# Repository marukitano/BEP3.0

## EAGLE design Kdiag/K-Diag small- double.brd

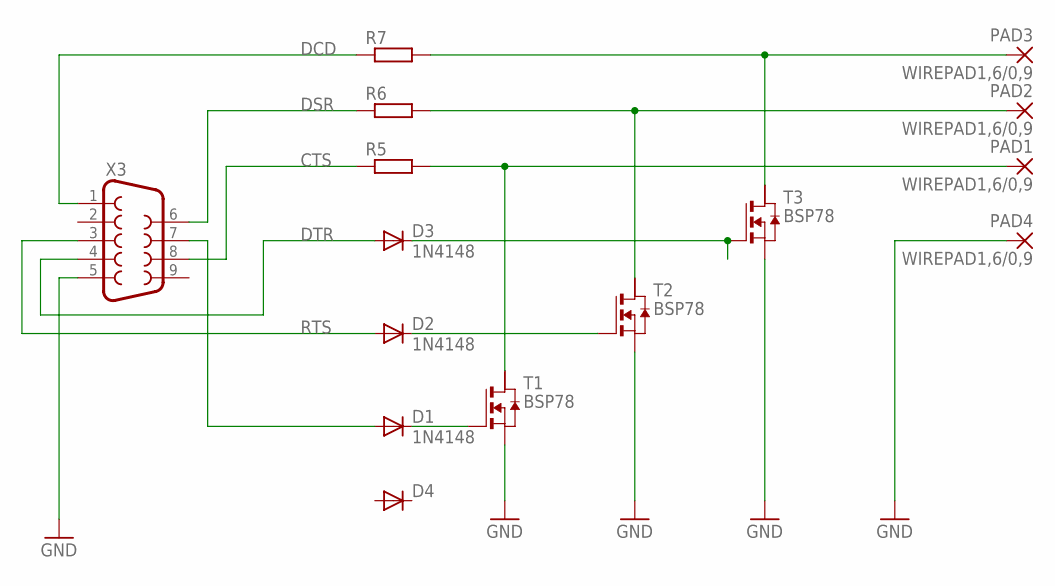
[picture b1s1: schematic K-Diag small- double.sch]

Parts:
D1, D2, D3: 1N4148; SOD323-W
D4: DIODE-SOD323-W; SOD323-W
PAD1, PAD2, PAD3, PAD4: WIREPAD1,6/0,9; 1,6/0,9
R5, R6, R7: R-EU_R0805; R0805
T1, T2, T3: BSP78; SOT223
X3: F09D

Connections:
CTS: R5.1, X3.8
DCD: R7.1, X3.1
DSR: R6.1, X3.6
DTR: D3.A, X3.4
GND: PAD4.1, T1.3 (S), T2.3 (S), T3.3 (S), X3.5
unnamed: D3.C, T3.1 (G)
unnamed: D2.C, T2.1 (G)
unnamed: D1.C, T1.1 (G)
unnamed: PAD1.1, R5.2, T1.2 (D)
unnamed: PAD2.1, R6.2, T2.2 (D)
unnamed: PAD3.1, R7.2, T3.2 (D)
unnamed: D1.A, X3.7
RTS: D2.A, X3.3

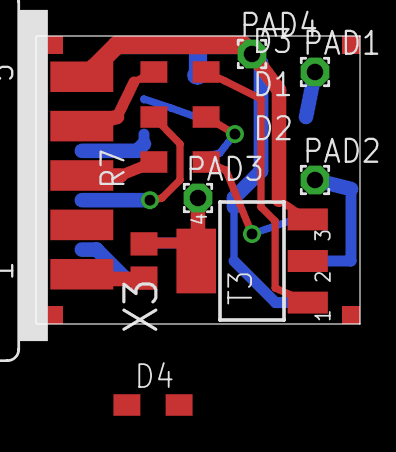
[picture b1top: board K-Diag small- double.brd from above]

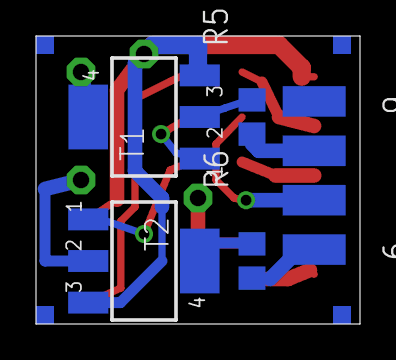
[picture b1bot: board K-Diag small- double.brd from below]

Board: 2 copper layers, 18.0 x 16.0 mm, 15 parts (4 on the bottom side), 13 nets.

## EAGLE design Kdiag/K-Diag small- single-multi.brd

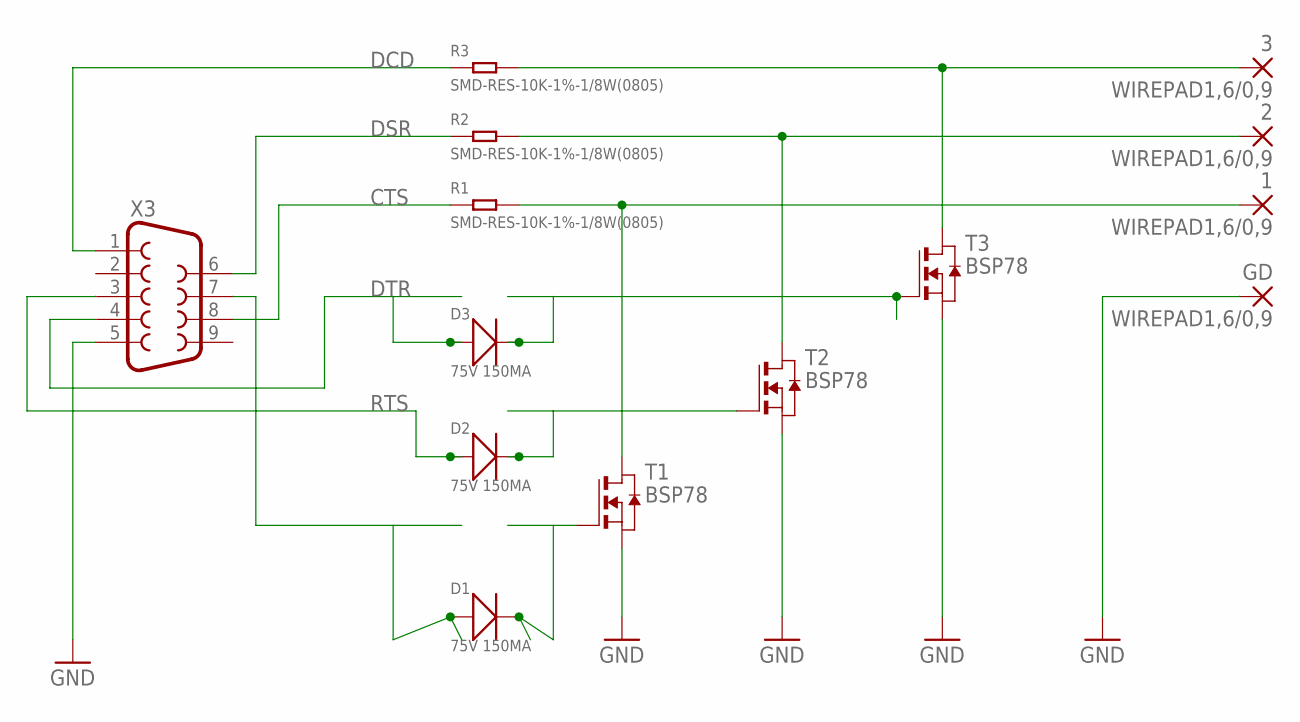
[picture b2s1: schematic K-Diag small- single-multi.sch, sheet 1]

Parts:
1, 2, 3: WIREPAD1,6/0,9; 1,6/0,9
D1, D2, D3: 75V 150MA; LED-1206
GD: WIREPAD1,6/0,9; 1,6/0,9
R1, R2, R3: SMD-RES-10K-1%-1/8W(0805); R0805
T1, T2, T3: BSP78; SOT223
X3: F09D

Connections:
CTS: R1.1, X3.8; also elsewhere on the board
DCD: R3.1, X3.1; also elsewhere on the board
DSR: R2.1, X3.6; also elsewhere on the board
DTR: D3.+, X3.4; also elsewhere on the board
GND: GD.1, T1.3 (S), T2.3 (S), T3.3 (S), X3.5; also elsewhere on the board
unnamed: D3.-, T3.1 (G)
unnamed: D2.-, T2.1 (G)
unnamed: D1.-, T1.1 (G)
unnamed: 1.1, R1.2, T1.2 (D), T1.4 (D)
unnamed: 2.1, R2.2, T2.2 (D), T2.4 (D)
unnamed: 3.1, R3.2, T3.2 (D), T3.4 (D)
unnamed: D1.+, X3.7
RTS: D2.+, X3.3; also elsewhere on the board

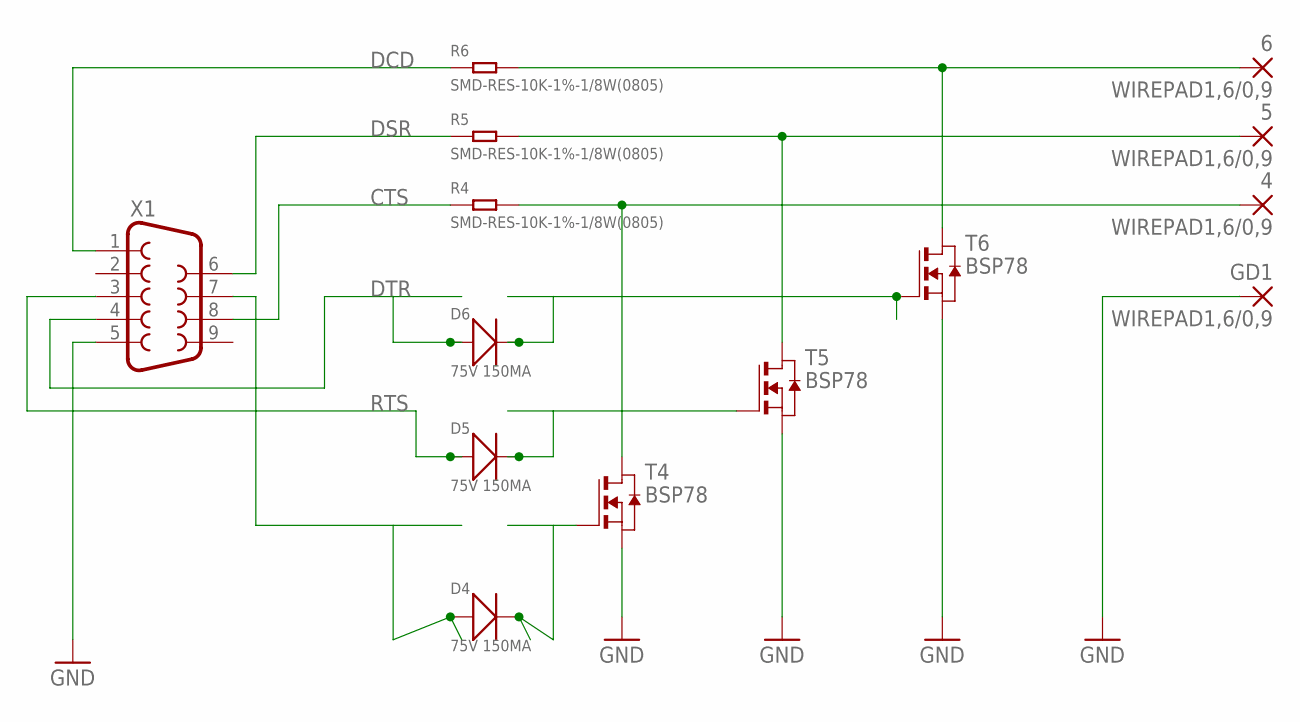
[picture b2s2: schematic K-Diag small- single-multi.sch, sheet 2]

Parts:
4, 5, 6: WIREPAD1,6/0,9; 1,6/0,9
D4, D5, D6: 75V 150MA; LED-1206
GD1: WIREPAD1,6/0,9; 1,6/0,9
R4, R5, R6: SMD-RES-10K-1%-1/8W(0805); R0805
T4, T5, T6: BSP78; SOT223
X1: F09D

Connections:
CTS: R4.1, X1.8; also elsewhere on the board
DCD: R6.1, X1.1; also elsewhere on the board
DSR: R5.1, X1.6; also elsewhere on the board
DTR: D6.+, X1.4; also elsewhere on the board
GND: GD1.1, T4.3 (S), T5.3 (S), T6.3 (S), X1.5; also elsewhere on the board
unnamed: D6.-, T6.1 (G)
unnamed: D5.-, T5.1 (G)
unnamed: D4.-, T4.1 (G)
unnamed: 4.1, R4.2, T4.2 (D), T4.4 (D)
unnamed: 5.1, R5.2, T5.2 (D), T5.4 (D)
unnamed: 6.1, R6.2, T6.2 (D), T6.4 (D)
unnamed: D4.+, X1.7
RTS: D5.+, X1.3; also elsewhere on the board

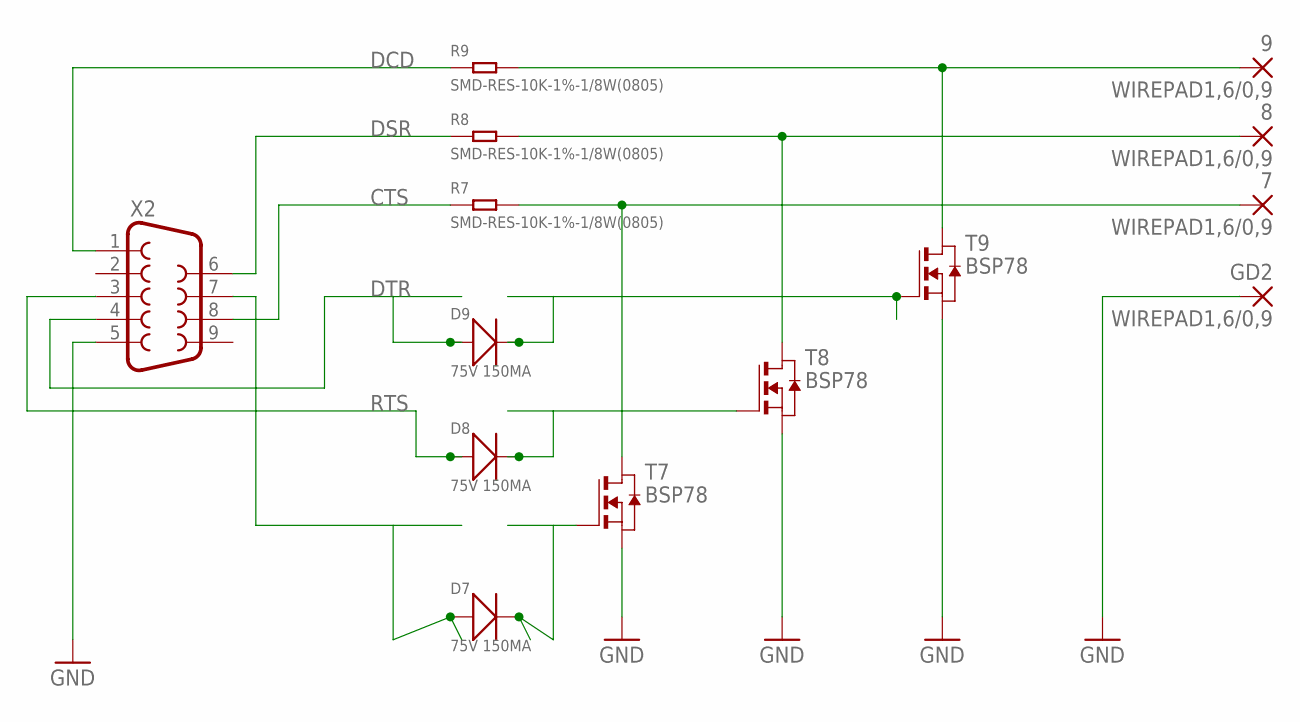
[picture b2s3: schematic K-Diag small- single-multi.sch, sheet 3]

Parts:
7, 8, 9: WIREPAD1,6/0,9; 1,6/0,9
D7, D8, D9: 75V 150MA; LED-1206
GD2: WIREPAD1,6/0,9; 1,6/0,9
R7, R8, R9: SMD-RES-10K-1%-1/8W(0805); R0805
T7, T8, T9: BSP78; SOT223
X2: F09D

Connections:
CTS: R7.1, X2.8; also elsewhere on the board
DCD: R9.1, X2.1; also elsewhere on the board
DSR: R8.1, X2.6; also elsewhere on the board
DTR: D9.+, X2.4; also elsewhere on the board
GND: GD2.1, T7.3 (S), T8.3 (S), T9.3 (S), X2.5; also elsewhere on the board
unnamed: D9.-, T9.1 (G)
unnamed: D8.-, T8.1 (G)
unnamed: D7.-, T7.1 (G)
unnamed: 7.1, R7.2, T7.2 (D), T7.4 (D)
unnamed: 8.1, R8.2, T8.2 (D), T8.4 (D)
unnamed: 9.1, R9.2, T9.2 (D), T9.4 (D)
unnamed: D7.+, X2.7
RTS: D8.+, X2.3; also elsewhere on the board

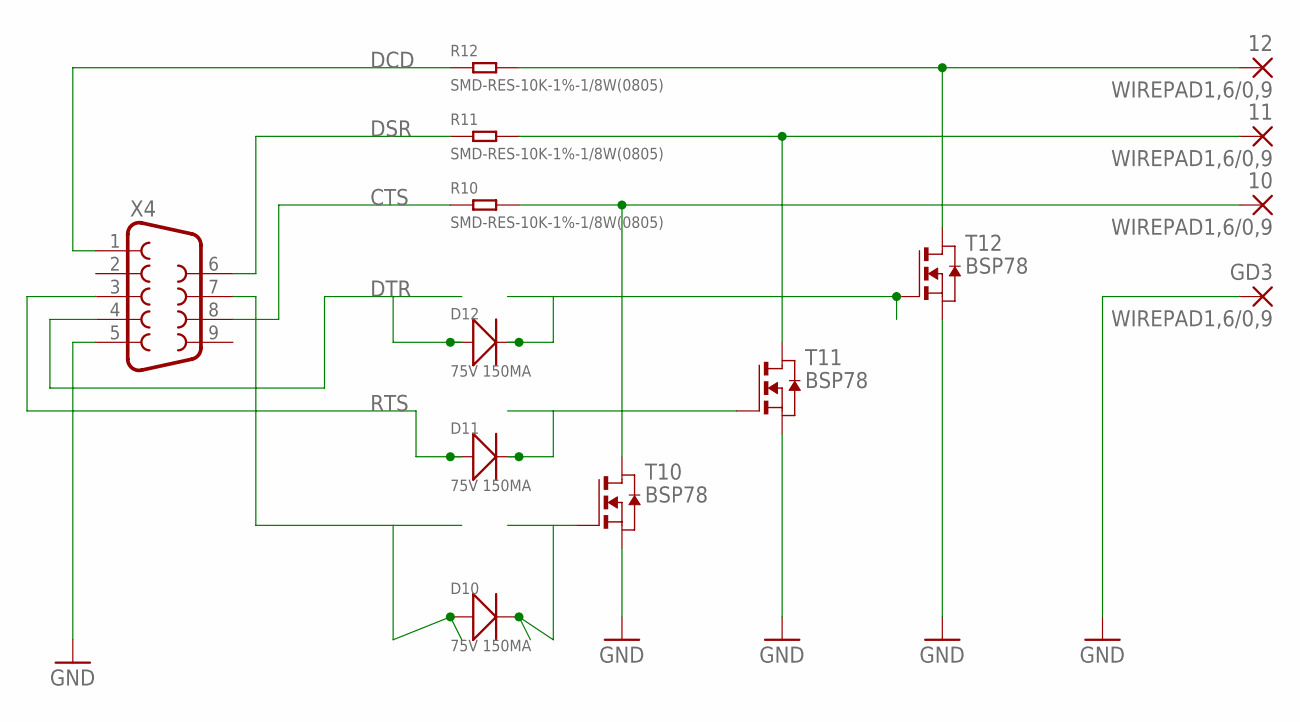
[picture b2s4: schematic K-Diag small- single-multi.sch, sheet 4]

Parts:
10, 11, 12: WIREPAD1,6/0,9; 1,6/0,9
D10, D11, D12: 75V 150MA; LED-1206
GD3: WIREPAD1,6/0,9; 1,6/0,9
R10, R11, R12: SMD-RES-10K-1%-1/8W(0805); R0805
T10, T11, T12: BSP78; SOT223
X4: F09D

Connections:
CTS: R10.1, X4.8; also elsewhere on the board
DCD: R12.1, X4.1; also elsewhere on the board
DSR: R11.1, X4.6; also elsewhere on the board
DTR: D12.+, X4.4; also elsewhere on the board
GND: GD3.1, T10.3 (S), T11.3 (S), T12.3 (S), X4.5; also elsewhere on the board
unnamed: D12.-, T12.1 (G)
unnamed: D11.-, T11.1 (G)
unnamed: D10.-, T10.1 (G)
unnamed: 10.1, R10.2, T10.2 (D), T10.4 (D)
unnamed: 11.1, R11.2, T11.2 (D), T11.4 (D)
unnamed: 12.1, R12.2, T12.2 (D), T12.4 (D)
unnamed: D10.+, X4.7
RTS: D11.+, X4.3; also elsewhere on the board

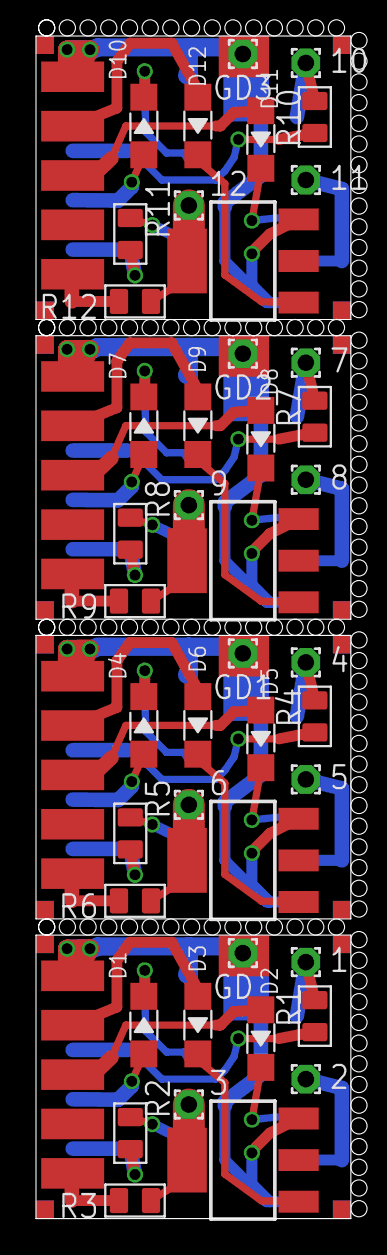
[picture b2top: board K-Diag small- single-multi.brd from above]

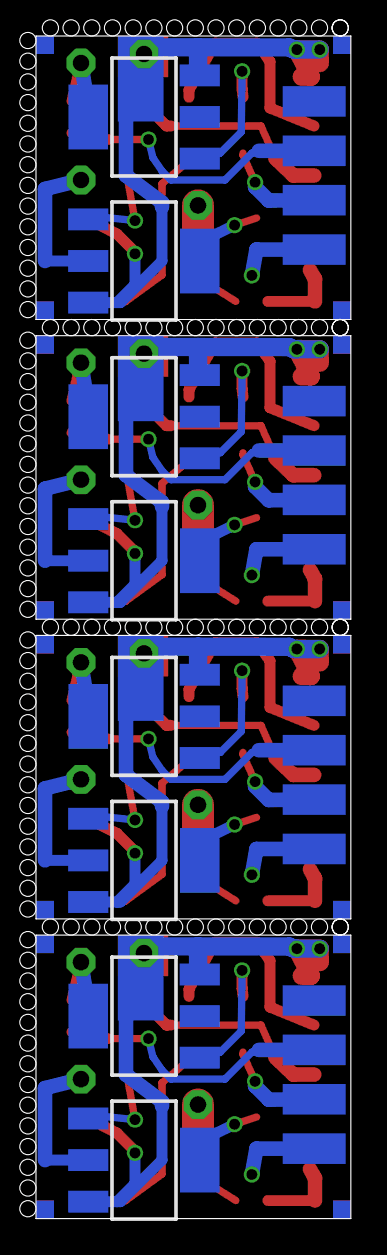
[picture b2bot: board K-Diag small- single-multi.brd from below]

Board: 2 copper layers, 17.5 x 65.7 mm, 56 parts (8 on the bottom side), 34 nets.

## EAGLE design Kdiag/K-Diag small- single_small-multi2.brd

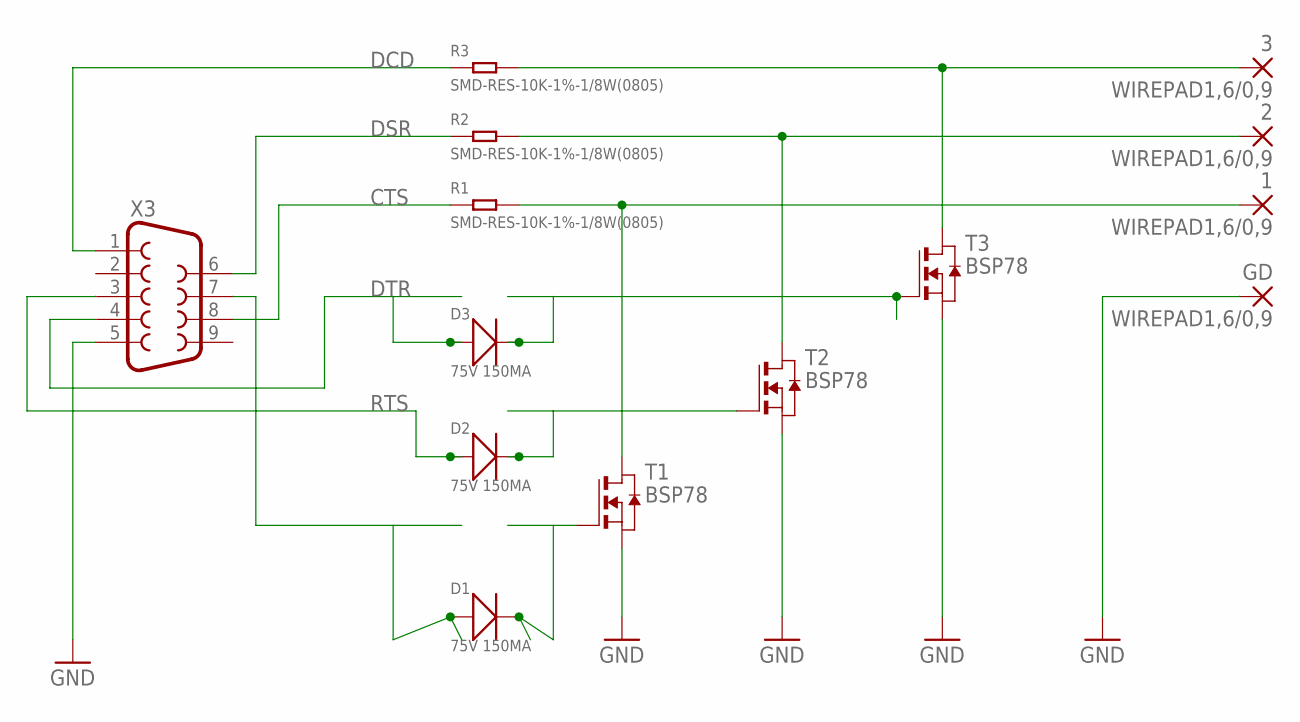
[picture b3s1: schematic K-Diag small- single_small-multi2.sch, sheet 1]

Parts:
1, 2, 3: WIREPAD1,6/0,9; 1,6/0,9
D1, D2, D3: 75V 150MA; LED-1206
GD: WIREPAD1,6/0,9; 1,6/0,9
R1, R2, R3: SMD-RES-10K-1%-1/8W(0805); R0805
T1, T2, T3: BSP78; SOT223
X3: F09D

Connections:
CTS: R1.1, X3.8; also elsewhere on the board
DCD: R3.1, X3.1; also elsewhere on the board
DSR: R2.1, X3.6; also elsewhere on the board
DTR: D3.+, X3.4; also elsewhere on the board
GND: GD.1, T1.3 (S), T2.3 (S), T3.3 (S), X3.5; also elsewhere on the board
unnamed: D3.-, T3.1 (G)
unnamed: D2.-, T2.1 (G)
unnamed: D1.-, T1.1 (G)
unnamed: 1.1, R1.2, T1.2 (D), T1.4 (D)
unnamed: 2.1, R2.2, T2.2 (D), T2.4 (D)
unnamed: 3.1, R3.2, T3.2 (D), T3.4 (D)
unnamed: D1.+, X3.7
RTS: D2.+, X3.3; also elsewhere on the board

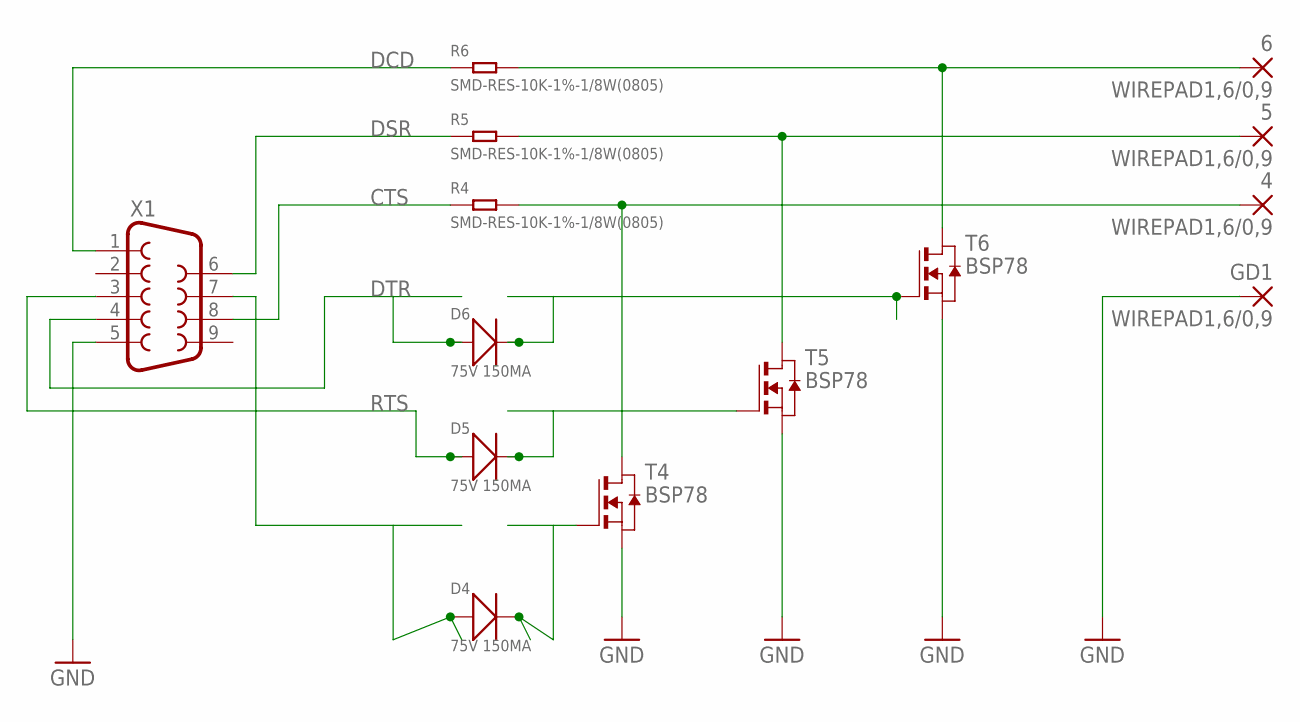
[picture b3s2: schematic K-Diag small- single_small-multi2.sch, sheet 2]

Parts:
4, 5, 6: WIREPAD1,6/0,9; 1,6/0,9
D4, D5, D6: 75V 150MA; LED-1206
GD1: WIREPAD1,6/0,9; 1,6/0,9
R4, R5, R6: SMD-RES-10K-1%-1/8W(0805); R0805
T4, T5, T6: BSP78; SOT223
X1: F09D

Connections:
CTS: R4.1, X1.8; also elsewhere on the board
DCD: R6.1, X1.1; also elsewhere on the board
DSR: R5.1, X1.6; also elsewhere on the board
DTR: D6.+, X1.4; also elsewhere on the board
GND: GD1.1, T4.3 (S), T5.3 (S), T6.3 (S), X1.5; also elsewhere on the board
unnamed: D6.-, T6.1 (G)
unnamed: D5.-, T5.1 (G)
unnamed: D4.-, T4.1 (G)
unnamed: 4.1, R4.2, T4.2 (D), T4.4 (D)
unnamed: 5.1, R5.2, T5.2 (D), T5.4 (D)
unnamed: 6.1, R6.2, T6.2 (D), T6.4 (D)
unnamed: D4.+, X1.7
RTS: D5.+, X1.3; also elsewhere on the board

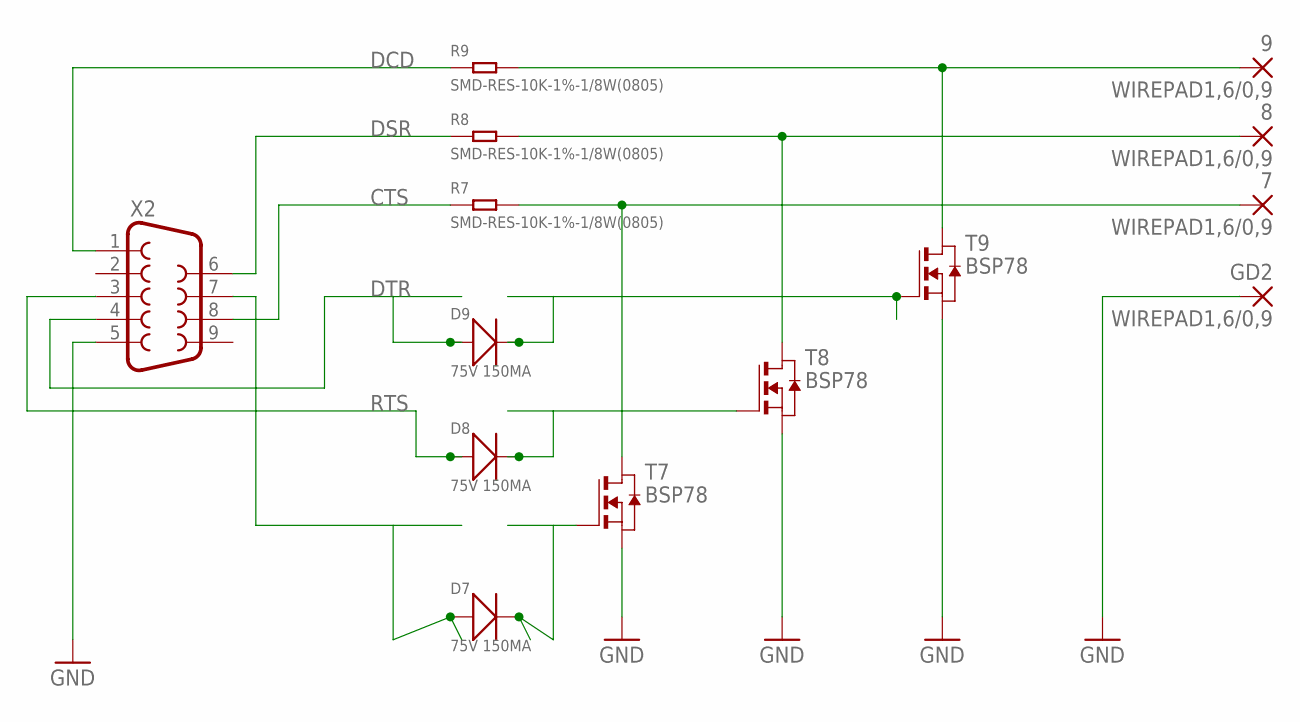
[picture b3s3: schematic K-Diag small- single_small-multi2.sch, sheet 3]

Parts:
7, 8, 9: WIREPAD1,6/0,9; 1,6/0,9
D7, D8, D9: 75V 150MA; LED-1206
GD2: WIREPAD1,6/0,9; 1,6/0,9
R7, R8, R9: SMD-RES-10K-1%-1/8W(0805); R0805
T7, T8, T9: BSP78; SOT223
X2: F09D

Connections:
CTS: R7.1, X2.8; also elsewhere on the board
DCD: R9.1, X2.1; also elsewhere on the board
DSR: R8.1, X2.6; also elsewhere on the board
DTR: D9.+, X2.4; also elsewhere on the board
GND: GD2.1, T7.3 (S), T8.3 (S), T9.3 (S), X2.5; also elsewhere on the board
unnamed: D9.-, T9.1 (G)
unnamed: D8.-, T8.1 (G)
unnamed: D7.-, T7.1 (G)
unnamed: 7.1, R7.2, T7.2 (D), T7.4 (D)
unnamed: 8.1, R8.2, T8.2 (D), T8.4 (D)
unnamed: 9.1, R9.2, T9.2 (D), T9.4 (D)
unnamed: D7.+, X2.7
RTS: D8.+, X2.3; also elsewhere on the board

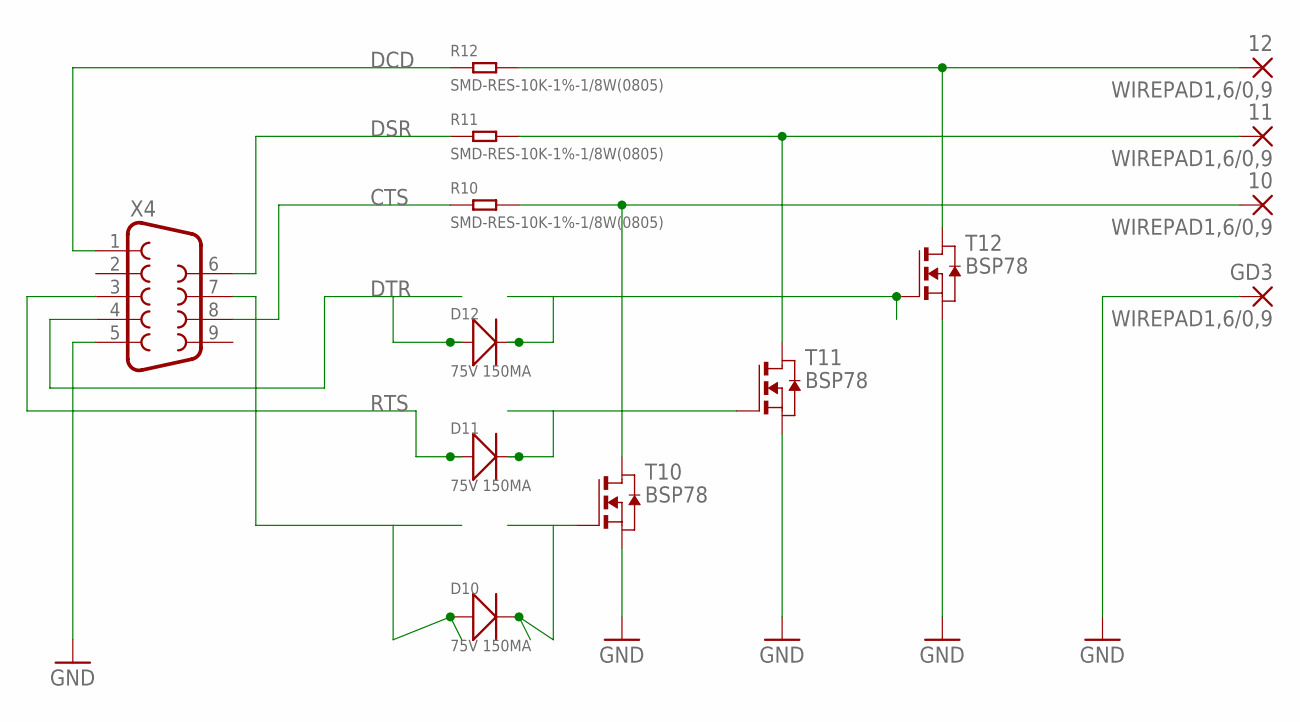
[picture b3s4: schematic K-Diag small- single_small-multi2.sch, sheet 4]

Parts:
10, 11, 12: WIREPAD1,6/0,9; 1,6/0,9
D10, D11, D12: 75V 150MA; LED-1206
GD3: WIREPAD1,6/0,9; 1,6/0,9
R10, R11, R12: SMD-RES-10K-1%-1/8W(0805); R0805
T10, T11, T12: BSP78; SOT223
X4: F09D

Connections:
CTS: R10.1, X4.8; also elsewhere on the board
DCD: R12.1, X4.1; also elsewhere on the board
DSR: R11.1, X4.6; also elsewhere on the board
DTR: D12.+, X4.4; also elsewhere on the board
GND: GD3.1, T10.3 (S), T11.3 (S), T12.3 (S), X4.5; also elsewhere on the board
unnamed: D12.-, T12.1 (G)
unnamed: D11.-, T11.1 (G)
unnamed: D10.-, T10.1 (G)
unnamed: 10.1, R10.2, T10.2 (D), T10.4 (D)
unnamed: 11.1, R11.2, T11.2 (D), T11.4 (D)
unnamed: 12.1, R12.2, T12.2 (D), T12.4 (D)
unnamed: D10.+, X4.7
RTS: D11.+, X4.3; also elsewhere on the board

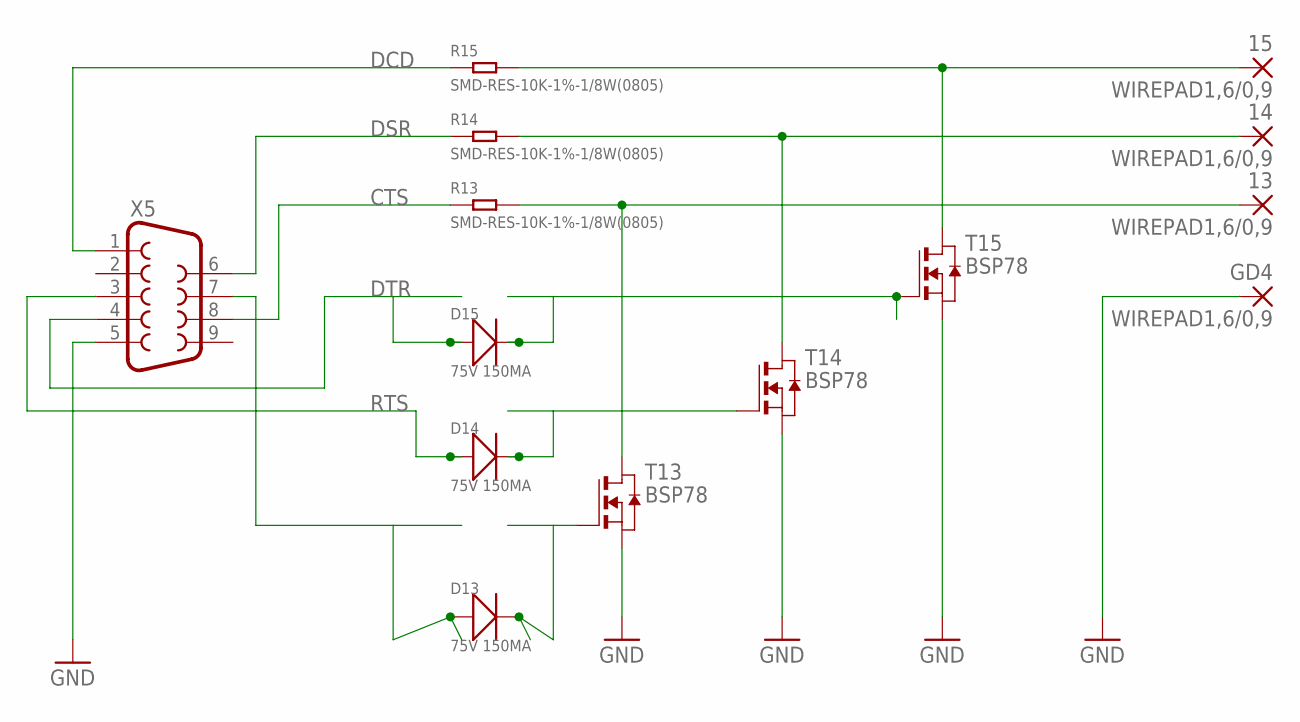
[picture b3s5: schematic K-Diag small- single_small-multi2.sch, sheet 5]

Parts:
13, 14, 15: WIREPAD1,6/0,9; 1,6/0,9
D13, D14, D15: 75V 150MA; LED-1206
GD4: WIREPAD1,6/0,9; 1,6/0,9
R13, R14, R15: SMD-RES-10K-1%-1/8W(0805); R0805
T13, T14, T15: BSP78; SOT223
X5: F09D

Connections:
CTS: R13.1, X5.8; also elsewhere on the board
DCD: R15.1, X5.1; also elsewhere on the board
DSR: R14.1, X5.6; also elsewhere on the board
DTR: D15.+, X5.4; also elsewhere on the board
GND: GD4.1, T13.3 (S), T14.3 (S), T15.3 (S), X5.5; also elsewhere on the board
unnamed: D15.-, T15.1 (G)
unnamed: D14.-, T14.1 (G)
unnamed: D13.-, T13.1 (G)
unnamed: 13.1, R13.2, T13.2 (D), T13.4 (D)
unnamed: 14.1, R14.2, T14.2 (D), T14.4 (D)
unnamed: 15.1, R15.2, T15.2 (D), T15.4 (D)
unnamed: D13.+, X5.7
RTS: D14.+, X5.3; also elsewhere on the board

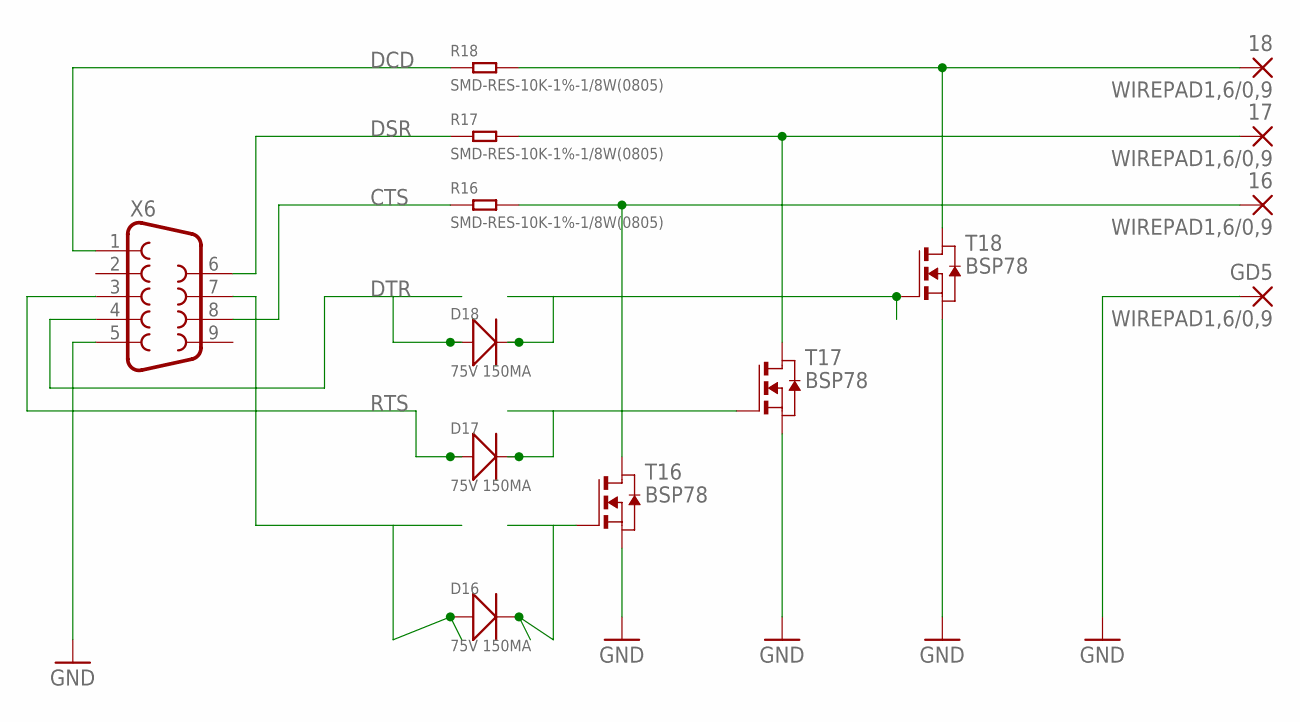
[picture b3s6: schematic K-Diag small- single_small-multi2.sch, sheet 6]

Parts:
16, 17, 18: WIREPAD1,6/0,9; 1,6/0,9
D16, D17, D18: 75V 150MA; LED-1206
GD5: WIREPAD1,6/0,9; 1,6/0,9
R16, R17, R18: SMD-RES-10K-1%-1/8W(0805); R0805
T16, T17, T18: BSP78; SOT223
X6: F09D

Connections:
CTS: R16.1, X6.8; also elsewhere on the board
DCD: R18.1, X6.1; also elsewhere on the board
DSR: R17.1, X6.6; also elsewhere on the board
DTR: D18.+, X6.4; also elsewhere on the board
GND: GD5.1, T16.3 (S), T17.3 (S), T18.3 (S), X6.5; also elsewhere on the board
unnamed: D18.-, T18.1 (G)
unnamed: D17.-, T17.1 (G)
unnamed: D16.-, T16.1 (G)
unnamed: 16.1, R16.2, T16.2 (D), T16.4 (D)
unnamed: 17.1, R17.2, T17.2 (D), T17.4 (D)
unnamed: 18.1, R18.2, T18.2 (D), T18.4 (D)
unnamed: D16.+, X6.7
RTS: D17.+, X6.3; also elsewhere on the board

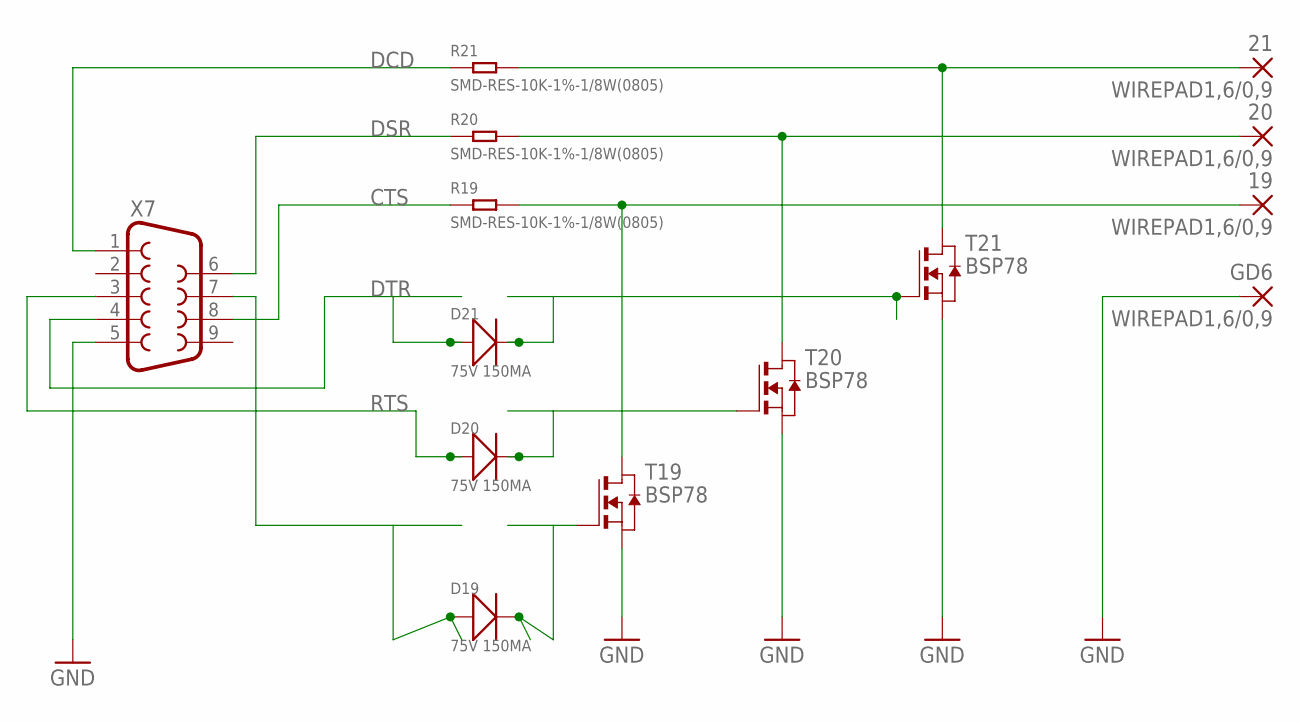
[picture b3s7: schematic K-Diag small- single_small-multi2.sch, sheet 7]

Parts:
19, 20, 21: WIREPAD1,6/0,9; 1,6/0,9
D19, D20, D21: 75V 150MA; LED-1206
GD6: WIREPAD1,6/0,9; 1,6/0,9
R19, R20, R21: SMD-RES-10K-1%-1/8W(0805); R0805
T19, T20, T21: BSP78; SOT223
X7: F09D

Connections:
CTS: R19.1, X7.8; also elsewhere on the board
DCD: R21.1, X7.1; also elsewhere on the board
DSR: R20.1, X7.6; also elsewhere on the board
DTR: D21.+, X7.4; also elsewhere on the board
GND: GD6.1, T19.3 (S), T20.3 (S), T21.3 (S), X7.5; also elsewhere on the board
unnamed: D21.-, T21.1 (G)
unnamed: D20.-, T20.1 (G)
unnamed: D19.-, T19.1 (G)
unnamed: 19.1, R19.2, T19.2 (D), T19.4 (D)
unnamed: 20.1, R20.2, T20.2 (D), T20.4 (D)
unnamed: 21.1, R21.2, T21.2 (D), T21.4 (D)
unnamed: D19.+, X7.7
RTS: D20.+, X7.3; also elsewhere on the board

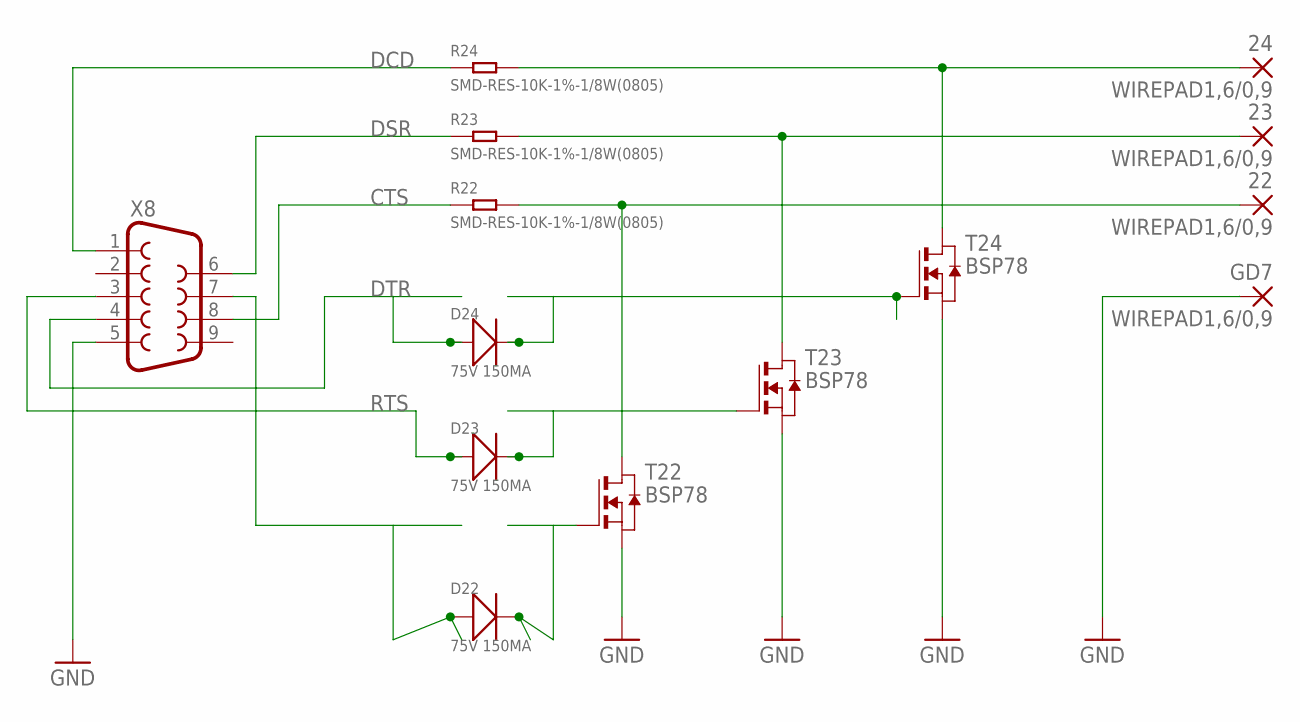
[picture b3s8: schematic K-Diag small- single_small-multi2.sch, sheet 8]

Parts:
22, 23, 24: WIREPAD1,6/0,9; 1,6/0,9
D22, D23, D24: 75V 150MA; LED-1206
GD7: WIREPAD1,6/0,9; 1,6/0,9
R22, R23, R24: SMD-RES-10K-1%-1/8W(0805); R0805
T22, T23, T24: BSP78; SOT223
X8: F09D

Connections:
CTS: R22.1, X8.8; also elsewhere on the board
DCD: R24.1, X8.1; also elsewhere on the board
DSR: R23.1, X8.6; also elsewhere on the board
DTR: D24.+, X8.4; also elsewhere on the board
GND: GD7.1, T22.3 (S), T23.3 (S), T24.3 (S), X8.5; also elsewhere on the board
unnamed: D24.-, T24.1 (G)
unnamed: D23.-, T23.1 (G)
unnamed: D22.-, T22.1 (G)
unnamed: 22.1, R22.2, T22.2 (D), T22.4 (D)
unnamed: 23.1, R23.2, T23.2 (D), T23.4 (D)
unnamed: 24.1, R24.2, T24.2 (D), T24.4 (D)
unnamed: D22.+, X8.7
RTS: D23.+, X8.3; also elsewhere on the board

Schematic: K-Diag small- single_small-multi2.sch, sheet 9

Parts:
25, 26, 27: WIREPAD1,6/0,9; 1,6/0,9
D25, D26, D27: 75V 150MA; LED-1206
GD8: WIREPAD1,6/0,9; 1,6/0,9
R25, R26, R27: SMD-RES-10K-1%-1/8W(0805); R0805
T25, T26, T27: BSP78; SOT223
X9: F09D

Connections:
CTS: R25.1, X9.8; also elsewhere on the board
DCD: R27.1, X9.1; also elsewhere on the board
DSR: R26.1, X9.6; also elsewhere on the board
DTR: D27.+, X9.4; also elsewhere on the board
GND: GD8.1, T25.3 (S), T26.3 (S), T27.3 (S), X9.5; also elsewhere on the board
unnamed: D27.-, T27.1 (G)
unnamed: D26.-, T26.1 (G)
unnamed: D25.-, T25.1 (G)
unnamed: 25.1, R25.2, T25.2 (D), T25.4 (D)
unnamed: 26.1, R26.2, T26.2 (D), T26.4 (D)
unnamed: 27.1, R27.2, T27.2 (D), T27.4 (D)
unnamed: D25.+, X9.7
RTS: D26.+, X9.3; also elsewhere on the board

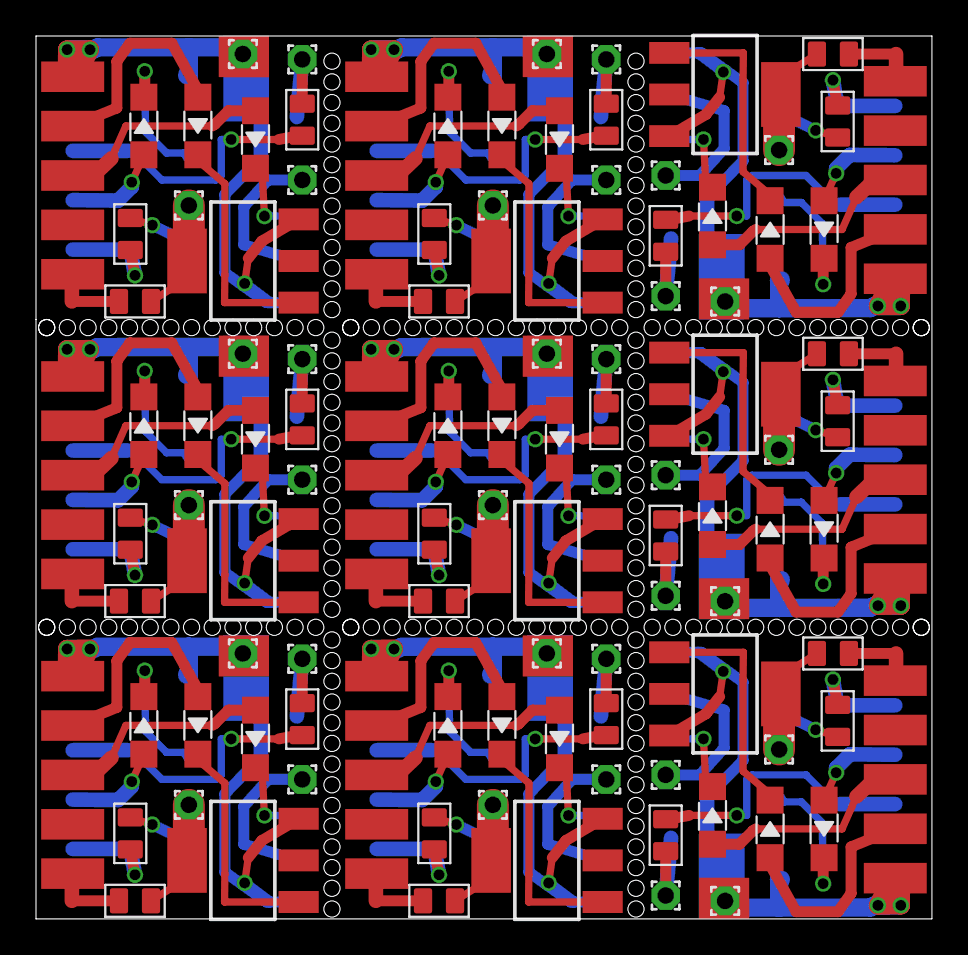
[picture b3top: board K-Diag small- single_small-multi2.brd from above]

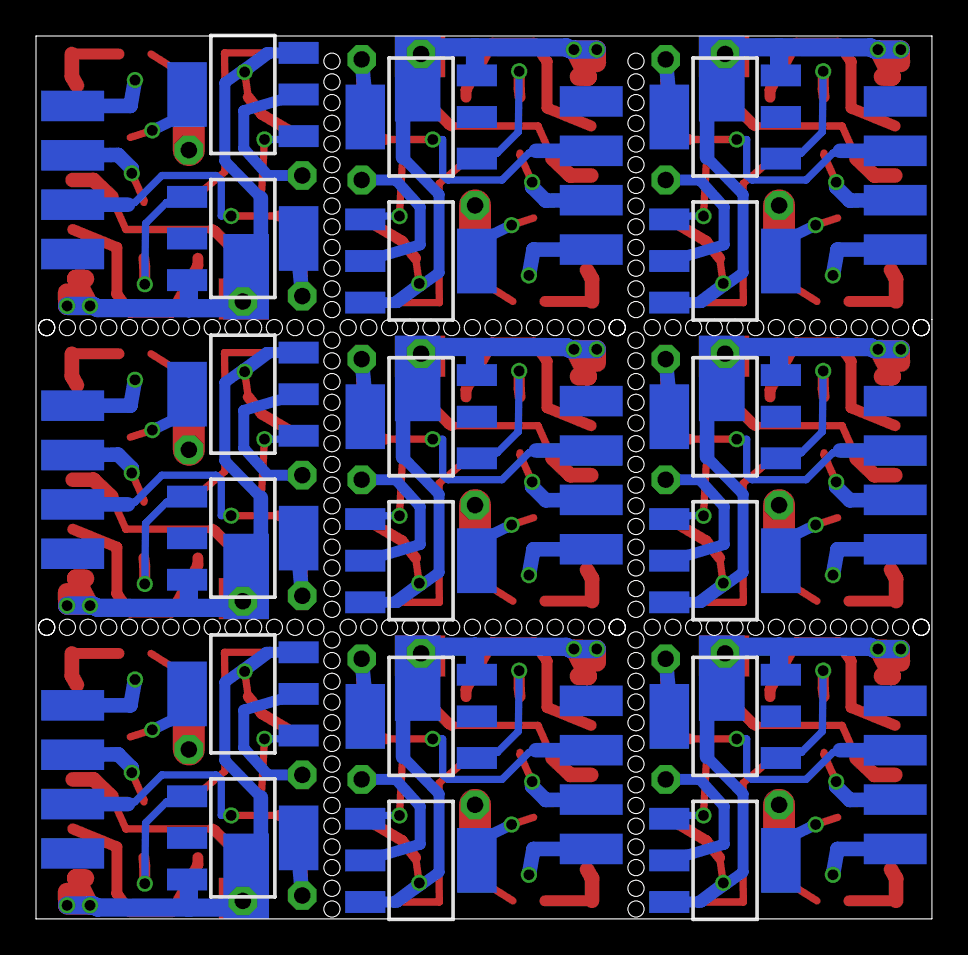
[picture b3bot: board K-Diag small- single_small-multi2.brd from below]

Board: 2 copper layers, 49.8 x 49.0 mm, 126 parts (18 on the bottom side), 69 nets.
